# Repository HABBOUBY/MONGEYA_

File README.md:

<div align="center">

# MONGEYA

### Smart Home Cleaning Station with an Autonomous Cleaning Robot

*A modular robotic ecosystem designed to automate repetitive household cleaning tasks.*

Built by **HABBOUBY EDEM** for [Beest](https://beest.hackclub.com/)

</div>

---

# About

MONGEYA is a smart cleaning station that automates several repetitive household tasks. It combines multiple cleaning systems inside a single machine and works together with **MONGY**, a compact autonomous robot that leaves the station to clean the floor before returning automatically to recharge.

The entire mechanical structure, electronics, and custom PCB were designed from scratch.

---

# Scope of This Submission

This submission covers the **mechanical design (CAD)** and the **custom PCB (KiCad)** for MONGEYA and Mongy. Firmware/embedded code is not included at this stage — this project is being submitted as a hardware and electronics design.

---

# ⚠️ Note on Physical Fabrication

This submission is provided as a **complete, print-ready CAD and PCB design** (STEP, STL, and KiCad project).

I do not currently have access to a 3D printer, and professional 3D printing services are costly and limited where I live (Tunisia). For this reason, I was not able to physically fabricate and photograph the assembled parts before submission.

Every file needed to reproduce MONGEYA and Mongy — including slicer-ready STL exports and print settings — is included in this repository, so the design can be fabricated and verified by anyone with access to a 3D printer.

**On 3D printing access in Tunisia:** Access to 3D printing hardware in Tunisia is particularly constrained. Import duties and customs taxes on 3D printers and electronics significantly raise their price compared to international markets, putting personal ownership out of reach for many students. Local makerspaces with printing capability are few, mostly concentrated in the capital, and operate as private, paid facilities with limited slots rather than open-access community labs. Online/local printing services exist but are costly and add delays for a project of this scale (multiple large structural parts). For these reasons, physical fabrication of MONGEYA and Mongy has not yet been possible, and the design is submitted as a complete, print-ready package so it can be reproduced and verified by anyone with printer access.

**Consequence for the live demo / playable version:** for the same reason, no live demo or playable version of the physical robot exists yet — there is no functioning hardware to record or interact with. In place of a live demo, the **Demo URL** points to a CAD walkthrough (renders / exploded view / turntable) so reviewers can still see the design in motion and in detail.

---

# On AI Assistance

As this is my first time using GitHub to structure and share a project of this scale, I used AI assistance to help review this submission against the shipping guide requirements, research relevant resources, and refine parts of this documentation. All design work — CAD modeling, PCB design, and engineering decisions — is my own.

---

# Why I Built This

The inspiration behind MONGEYA comes from my mother.

Every day she spends a significant amount of time cleaning shoes, sorting waste, and handling repetitive household chores. I wanted to design a machine capable of taking over these repetitive tasks, giving her more free time while making home cleaning easier and smarter.

---

# Meet MONGY

MONGY is the autonomous cleaning robot inside MONGEYA.

MONGY leaves its docking station, cleans the surrounding area using multiple cleaning mechanisms, and automatically returns to recharge.

---

# Features

- Automatic waste sorting (aluminum / plastic / paper)
- Automatic chemical dispensing (bleach + cleaning gel)
- Shoe cleaning station
- Autonomous floor cleaning
- Automatic docking and locking mechanism
- Automatic battery charging
- LiDAR navigation
- PID motor control with encoders
- Custom ESP32 PCB
- Fully 3D printable mechanical design

---

# Hardware

## Main Controller
- ESP32-WROOM-32

## Navigation
- RPLIDAR
- Hall-effect magnetic encoders
- IR sensors

## Motors
- JGB37 DC gear motors
- MG995 servo motors
- MG90 metal gear servo

## Cleaning
- Roller brush
- 12V vacuum pump
- Two 12V dosing pumps

## Batteries
**MONGY** — Compact 3S LiPo battery
**MONGEYA** — Three independent 3S LiPo batteries powering different subsystems

---

# Dimensions

## MONGY

| Property | Value |
|----------|------:|
| Diameter | 210 mm |
| Height | 50 mm |
| Weight | ~2 kg |

## MONGEYA

| Property | Value |
|----------|------:|
| Length | 400 mm |
| Width | 400 mm |
| Height | 600 mm |
| Weight | ~15 kg |

---

# 📦 Physical Scale Mockup (1:3.5)

While a full-scale 3D print of MONGEYA was not possible for the reasons explained above (no 3D printer access, high import costs on electronics/printers in Tunisia), a physical **1:3.5 scale cardboard mockup** was built by hand to demonstrate the real-world footprint, proportions, and general layout of the station.

This mockup shows:
- The overall enclosure shape and footprint of MONGEYA
- The docking bay where Mongy sits when charging
- The general internal cavity arrangement

It is **not a functional prototype** — no electronics, sensors, or motors are installed — but it serves as tangible, physical proof of the design's real-world scale and proportions, complementing the CAD renders and STL/STEP files included in this repository.

---

# 3D Printing

## Materials
- ABS for structural and high-stress components
- PLA for lightweight and cosmetic parts

## Recommended Print Settings

| Setting | Value |
|---------|------|
| Layer Height | 0.20 mm |
| Nozzle | 0.4 mm |
| Infill | 20% |
| Walls | 3 |
| Supports | Only where needed |

---

# Fasteners

| Screw | Quantity |
|-------|---------:|
| M3 × 10 mm | 25 |
| M3 × 13 mm | 15 |
| M3 × 15 mm | 15 |
| M3 × 19 mm | 5 |

Total: **60 M3 screws**

---

# Electronics

MONGY uses a custom PCB designed in **KiCad** around the **ESP32-WROOM-32**.

The `02_PCB/mongy/` folder contains:
- Fabrication files (Gerbers, drill files) — `FABRICATION/`
- Component list

The MONGEYA station intentionally uses modular perfboards for auxiliary circuits such as chemical dispensing and opto-isolated interfaces, making maintenance and future upgrades easier.

---

# Repository Structure

```text
mongeya-main/
│
├── 01_3D/
│   ├── SOLIDWORKS PARTS/
│   │   ├── MONGEYA & MONGY solidworks parts/   # Full native source — Mongy lives inside MONGEYA, so its parts are bundled here too 
│   │   ├── MONGY solidworks parts/              # Standalone native source for Mongy only
│   │   ├── protection system/
│   │  
│   │
│   │
│   ├── STL/
│   │   ├── STL FILES MONGEYA/
│   │   └── STL MONGY/
│   │
│   ├── cleaning robot mongySTEP/                # STEP source for Mongy only — the standalone cleaning robot, separate from the station
│   └── main station mongeyaSTEP.rar             # Single .rar — this assembly is a single (but heavy) STEP file, zipped to keep the repo light
│
├── 02_PCB/
│   └── mongy/
│       ├── FABRICATION/     # Gerbers + drill files
│       └── Component list PCB DESIGN.xlsx
│
├── 03_docs/
│   ├── CAD different view/
│   ├── renders/
│   ├── wiring/
│   └── PRESENTATION.pdf
│
├── 04_media/
|   └── cardboard_mockup.jpg
│   └── hero.png
|   
│
└── README.md
```

**On the "MONGEYA & MONGY solidworks parts" folder:** since Mongy physically docks and lives inside MONGEYA (it's the little robot that comes out of the big station, hihi 🐢🏠), the full combined SolidWorks source for both is kept together in one folder — this is the one to open if you want the complete ecosystem in a single assembly. The separate **"MONGY solidworks parts"** folder exists for anyone who only wants to reproduce the standalone cleaning robot on its own, without the station.

**On `cleaning robot mongySTEP`:** this folder holds the STEP export specifically for Mongy alone — useful if you just want to print/inspect the robot without pulling in the whole MONGEYA station.

**Note on file compression:** The `main station mongeya` assembly is provided as a single `.rar` because it is one large STEP file — zipping it keeps the repository lighter and faster to clone. It can be extracted with any standard tool (WinRAR, 7-Zip, The Unarchiver), and the STEP file inside remains fully editable in any CAD application. The STL exports are already slicer-ready as-is, no extraction needed beyond opening the STL folders.

---

# Assembly

1. Print all STL files (`01_3D/STL/`) using the settings above.
2. Assemble the mechanical structure using the specified M3 screws — see renders in `03_docs/renders/`.
3. Install the motors, pumps, and sensors.
4. Mount the custom PCB inside Mongy.
5. Connect batteries and wiring — see `03_docs/wiring/`.
6. Dock Mongy inside MONGEYA.

---

# CAD Files

This repository includes:
- **STEP files** — `01_3D/cleaning robot mongySTEP/` for Mongy, and `01_3D/main station mongeyaSTEP.rar` for MONGEYA, fully editable in any CAD tool
- **Native SolidWorks source** — `01_3D/SOLIDWORKS PARTS/`, split into the combined MONGEYA+MONGY assembly and the standalone Mongy parts
- **STL files** — `01_3D/STL/`, ready to slice and print

allowing anyone to modify, remix, or reproduce the project.

---

# Renders

---

# Documentation

Additional documentation is available inside `03_docs/`, including:
- Project presentation (`PRESENTATION.pdf`)
- CAD views and renders (`CAD different view/`, `renders/`)
- Wiring diagrams (`wiring/`)

---

# Future Improvements

- AI-based object recognition
- Automatic water refill
- Mobile application
- Voice assistant integration
- Multi-room navigation
- Firmware development (navigation, sorting logic, PID tuning)

---

# License

This project is released under the **MIT License**.

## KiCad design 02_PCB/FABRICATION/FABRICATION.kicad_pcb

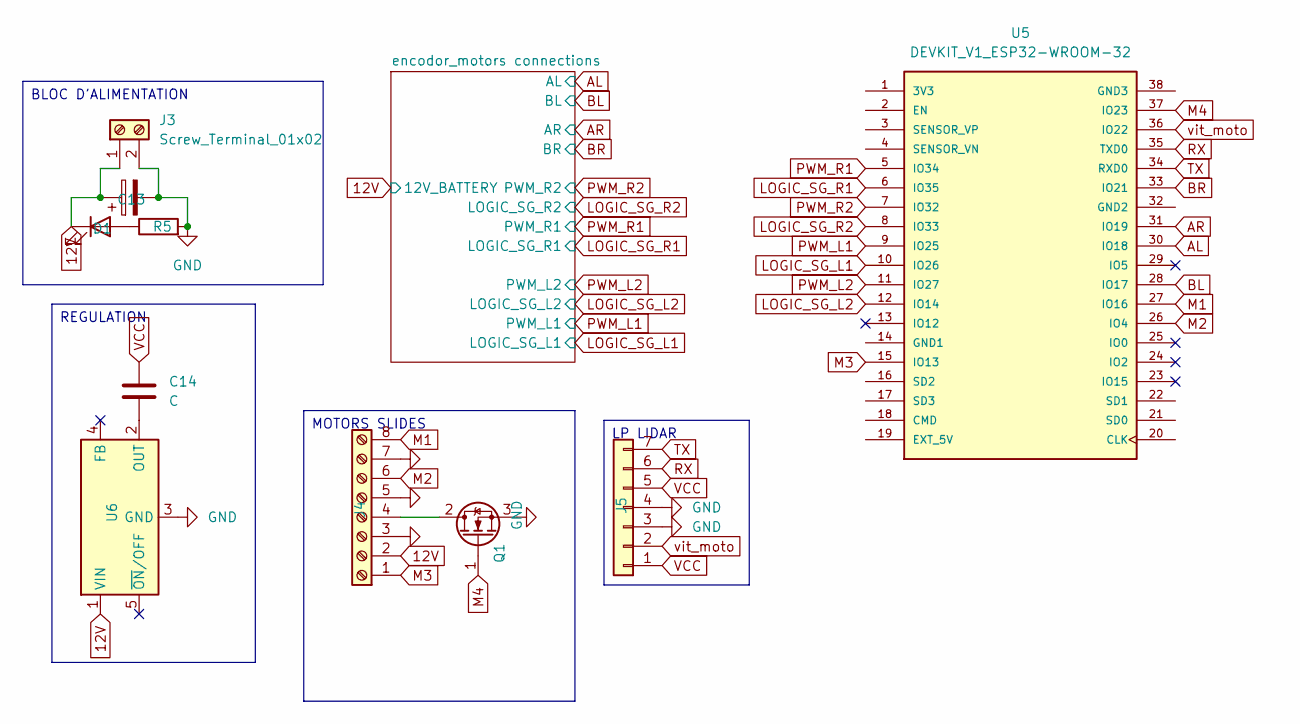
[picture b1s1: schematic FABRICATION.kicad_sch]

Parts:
C13: C_Polarized; C_Radial_D4.0mm_H5.0mm_P1.50mm
C14: C; C_Radial_D4.0mm_H5.0mm_P1.50mm
D1: LED; LED_D4.0mm
J3: Screw_Terminal_01x02; TerminalBlock_Phoenix_MKDS-1,5-2_1x02_P5.00mm_Horizontal
J4: Screw_Terminal_01x08; TerminalBlock_Phoenix_MKDS-1,5-8-5.08_1x08_P5.08mm_Horizont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
J5: Conn_01x07; PinHeader_1x07_P1.00mm_Vertical
Q1: IRLZ44N; TO-220-3_Vertical
R5: R; R_0603_1608Metric_Pad0.98x0.95mm_HandSolder
U5: DEVKIT_V1_ESP32-WROOM-32; MODULE_DEVKIT_V1_ESP32-WROOM-32; PARTREV N/A
U6: LM2596S-5; TO-263-5_TabPin3

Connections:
12V: C13.1, D1.1 (K), J3.1, J4.2, U6.1 (VIN); also elsewhere on the board
AL: U5.30 (IO18); also elsewhere on the board
AR: U5.31 (IO19); also elsewhere on the board
BL: U5.28 (IO17); also elsewhere on the board
BR: U5.33 (IO21); also elsewhere on the board
LOGIC_SG_L1: U5.10 (IO26); also elsewhere on the board
LOGIC_SG_L2: U5.12 (IO14); also elsewhere on the board
LOGIC_SG_R1: U5.6 (IO35); also elsewhere on the board
LOGIC_SG_R2: U5.8 (IO33); also elsewhere on the board
M1: J4.8, U5.27 (IO16)
M2: J4.6, U5.26 (IO4)
M3: J4.1, U5.15 (IO13)
M4: Q1.1 (G), U5.37 (IO23)
unnamed: D1.2 (A), R5.1
unnamed: J4.4, Q1.2 (D)
unnamed: C14.1, U6.2 (OUT)
PWM_L1: U5.9 (IO25); also elsewhere on the board
PWM_L2: U5.11 (IO27); also elsewhere on the board
PWM_R1: U5.5 (IO34); also elsewhere on the board
PWM_R2: U5.7 (IO32); also elsewhere on the board
RX: J5.6, U5.35 (TXD0)
TX: J5.7, U5.34 (RXD0)
VCC: C14.2, J5.1, J5.5; also elsewhere on the board
vit_moto: J5.2, U5.36 (IO22)

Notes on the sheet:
MOTORS SLIDES
REGULATION
LP LIDAR
BLOC D'ALIMENTATION

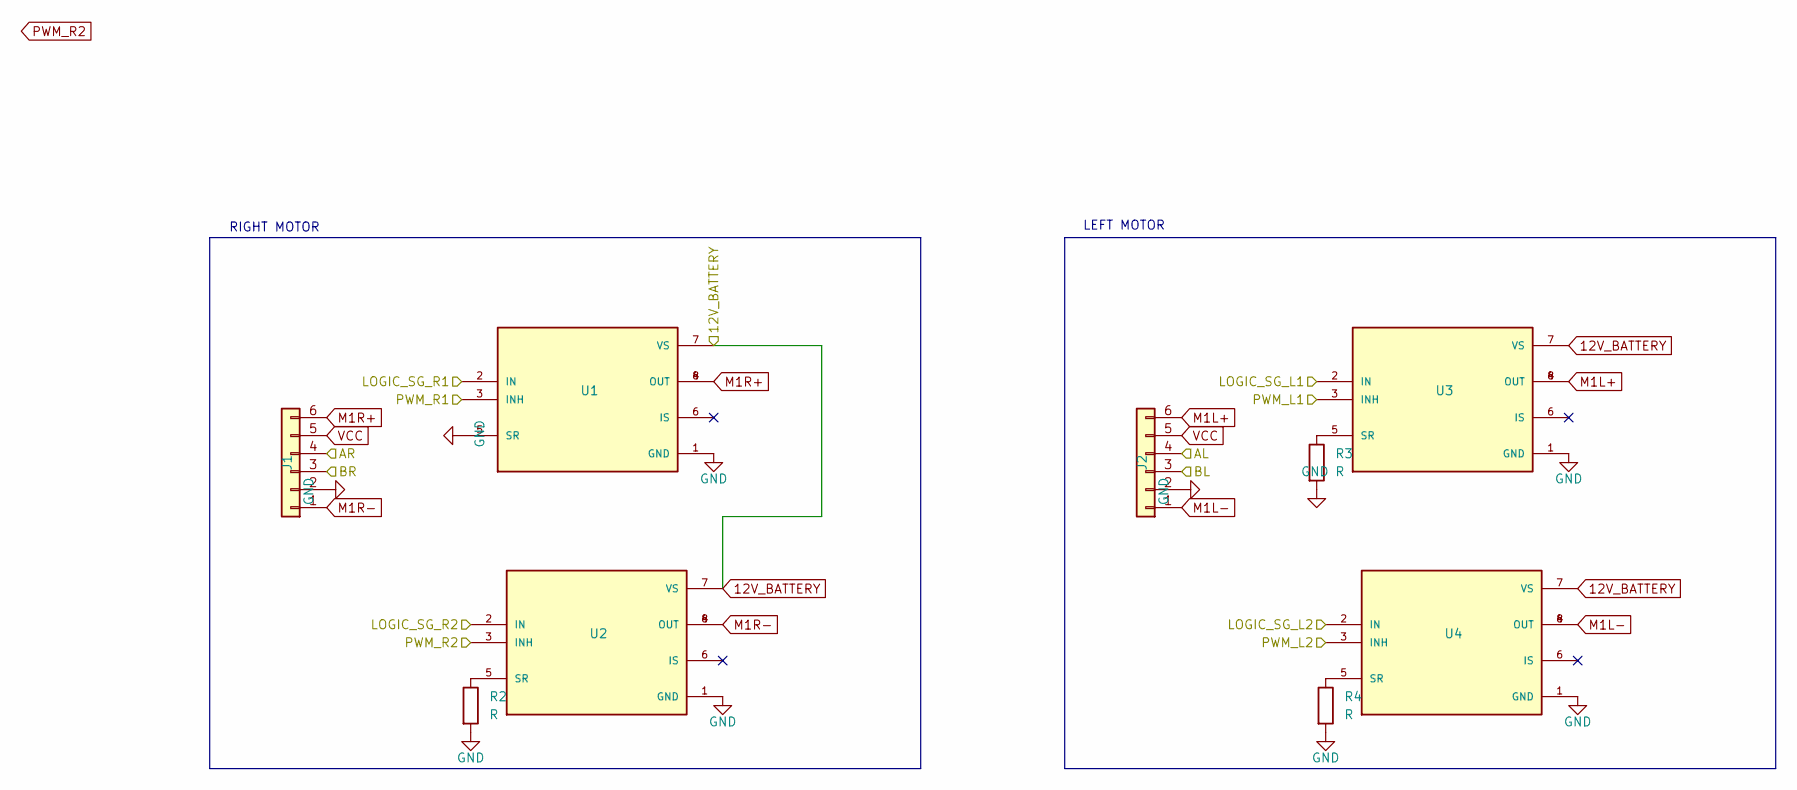
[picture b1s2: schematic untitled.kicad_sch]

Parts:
J1, J2: Conn_01x06; PinHeader_1x06_P1.00mm_Vertical
R2, R3, R4: R; R_0603_1608Metric_Pad0.98x0.95mm_HandSolder
U1, U2, U3, U4: BTN7960B; IC_BTN7960B; PARTREV 1.0

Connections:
12V: U1.7 (VS), U2.7 (VS), U3.7 (VS), U4.7 (VS); also elsewhere on the board
AL: J2.4; also elsewhere on the board
AR: J1.4; also elsewhere on the board
BL: J2.3; also elsewhere on the board
BR: J1.3; also elsewhere on the board
LOGIC_SG_L1: U3.2 (IN); also elsewhere on the board
LOGIC_SG_L2: U4.2 (IN); also elsewhere on the board
LOGIC_SG_R1: U1.2 (IN); also elsewhere on the board
LOGIC_SG_R2: U2.2 (IN); also elsewhere on the board
M1L+: J2.6, U3.4 (OUT), U3.8 (OUT)
M1L-: J2.1, U4.4 (OUT), U4.8 (OUT)
M1R+: J1.6, U1.4 (OUT), U1.8 (OUT)
M1R-: J1.1, U2.4 (OUT), U2.8 (OUT)
unnamed: R2.1, U2.5 (SR)
unnamed: R3.1, U3.5 (SR)
unnamed: R4.1, U4.5 (SR)
PWM_L1: U3.3 (INH); also elsewhere on the board
PWM_L2: U4.3 (INH); also elsewhere on the board
PWM_R1: U1.3 (INH); also elsewhere on the board
PWM_R2: U2.3 (INH); also elsewhere on the board
VCC: J1.5, J2.5; also elsewhere on the board

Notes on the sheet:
LEFT MOTOR
RIGHT MOTOR

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
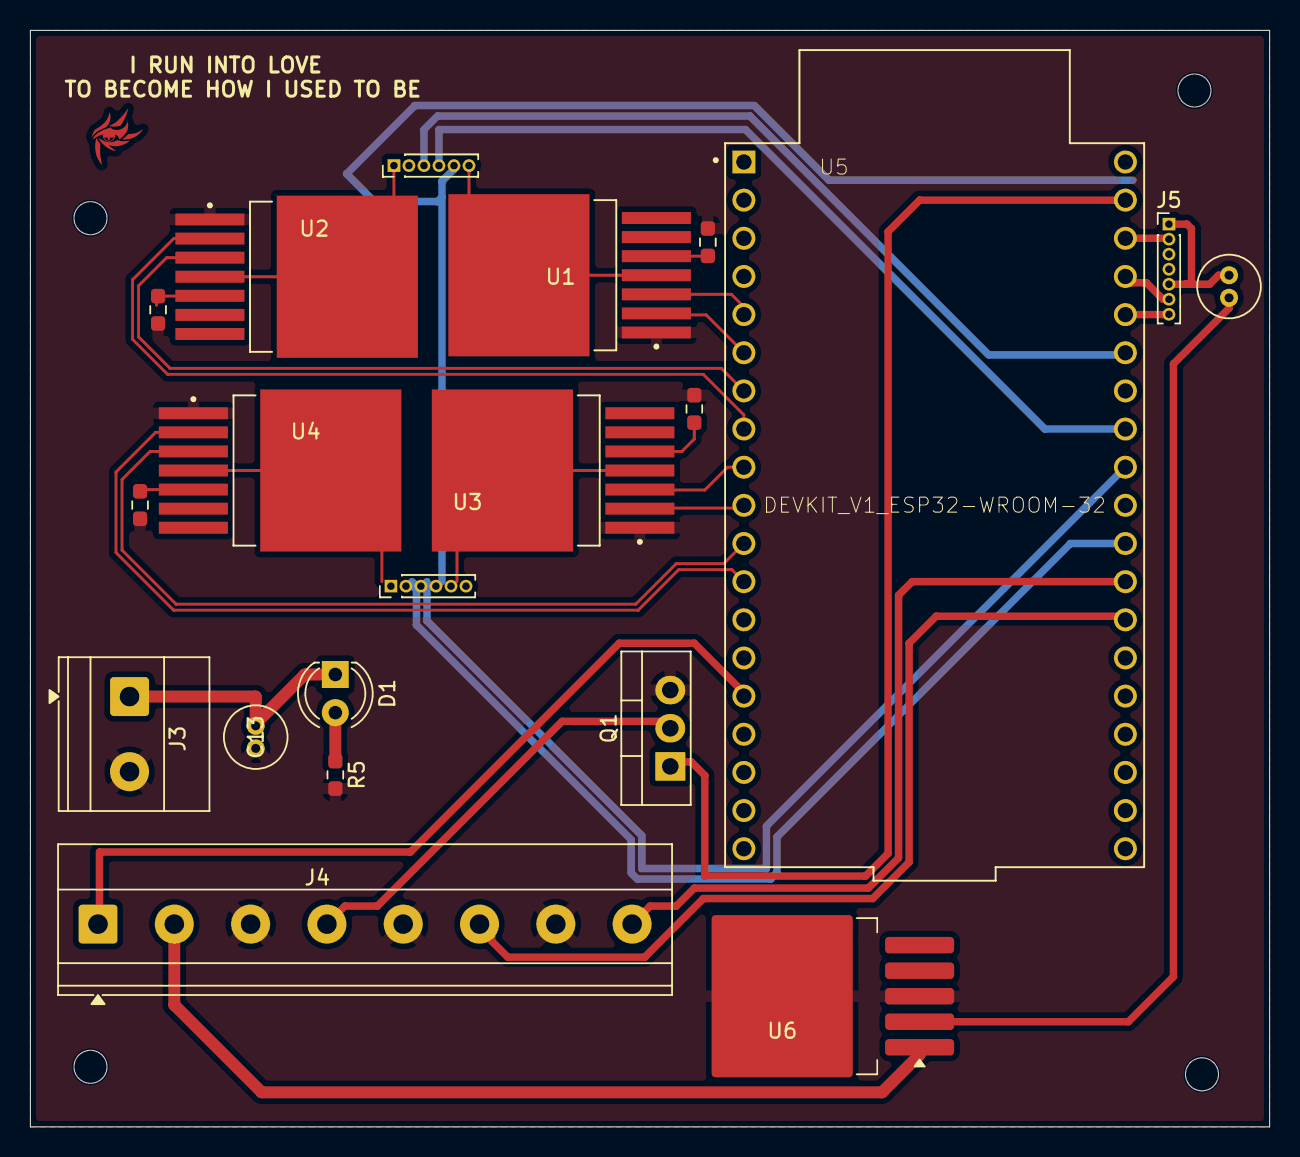
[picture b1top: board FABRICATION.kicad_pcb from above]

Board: 2 copper layers, 82.5 x 73.0 mm, 20 parts (0 on the bottom side), 33 nets.

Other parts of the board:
R1: R; R_0603_1608Metric_Pad0.98x0.95mm_HandSolder

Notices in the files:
README.md:
License: MIT
